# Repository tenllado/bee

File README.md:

# BEE board

A simple Raspberry pi expansion board, designed with educational purposes to be
used to learn low level IO programming or used it for simple driver development.
It adds to the raspberry Pi the following circuits:

- A 10 bits ADC with 8 channels (MCP3008), that can be connected to the SPI
  gpios using 5 jumpers, it is connected to CE0.

- A 10 bit DAC (MCP4911), that can also be connected to the SPI gpios using the
  same 5 jumpers, and gets connected to CE1.

- 3 simple led circuits, and 3 switch circuits that can be connected to any gpio
  pin with some cables.

- A piezo-electric buzzer that can be connected with jumpers to the pwm pins of
  the raspberry pi.

- A shifter register connected to 7 Segment display (with dot point).

- A UART connector for the FTDI-232-R cables to connect one of the UART devices
  of the Raspberry pi to a PC.

- A standard 20 pin JTAG connector for baremetal programming and in-circuit
  debug using OpenOCD.

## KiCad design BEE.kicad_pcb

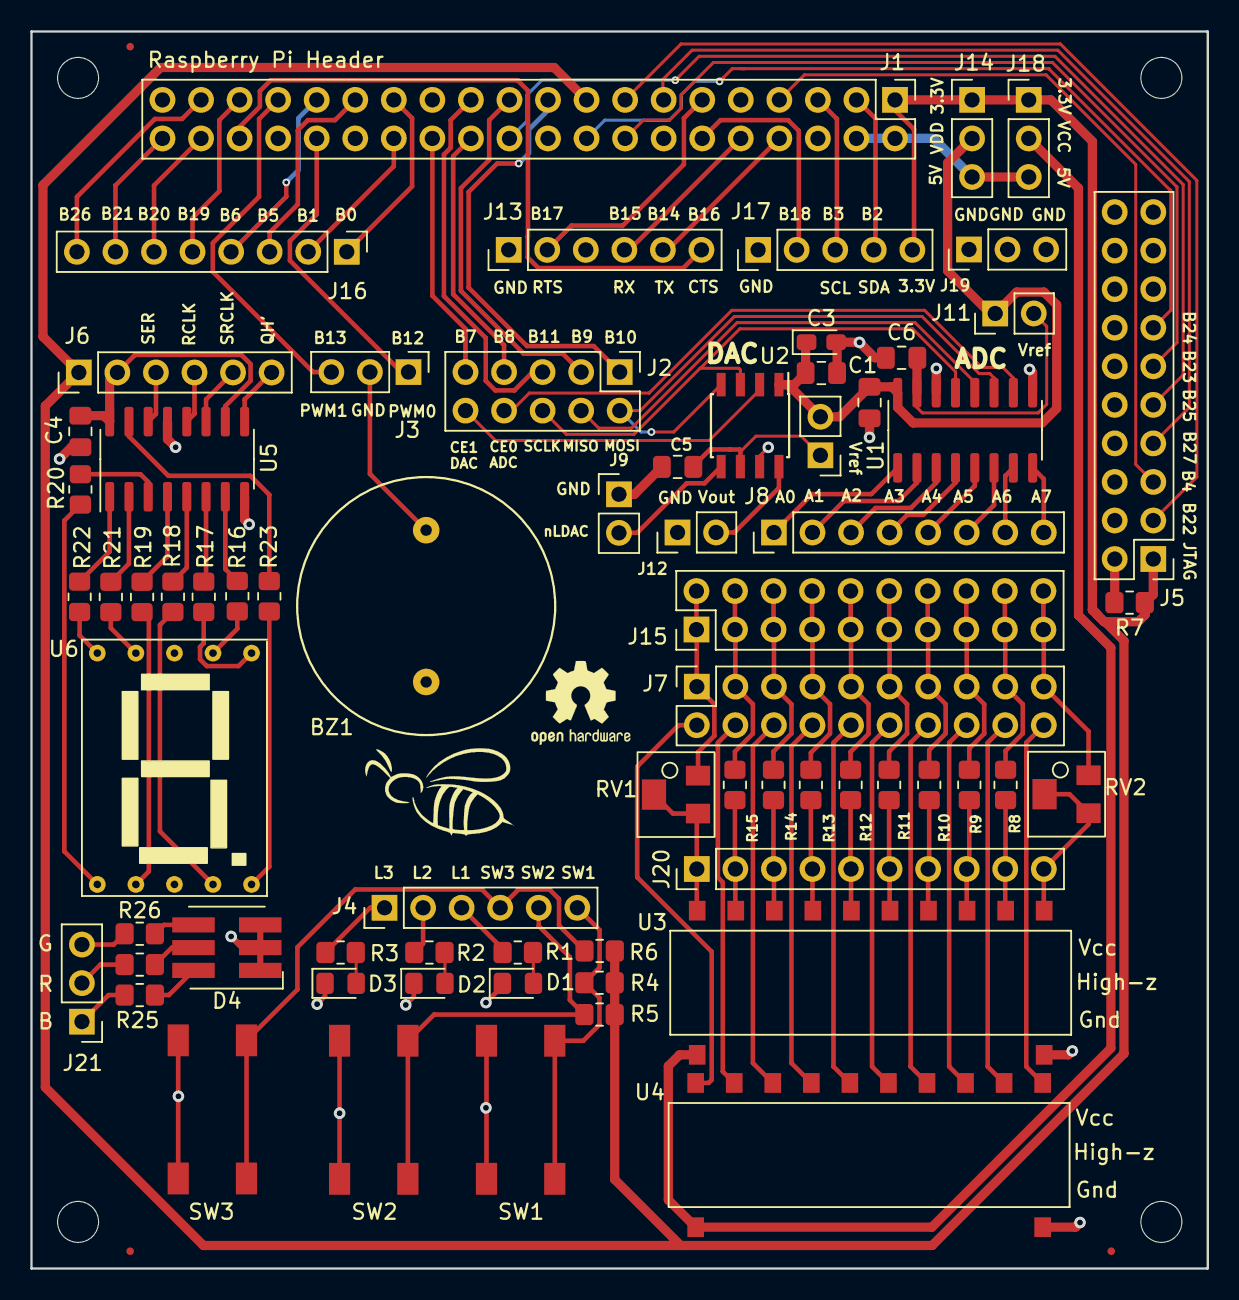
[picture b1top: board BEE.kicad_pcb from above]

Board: 2 copper layers, 77.5 x 81.5 mm, 79 parts (1 on the bottom side), 118 nets.

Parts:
BZ1: /re; Buzzer
C1, C6: 1uF; C_0805_2012Metric_Pad1.18x1.45mm_HandSolder
C2, C4, C5: 0.1uF; C_0805_2012Metric_Pad1.18x1.45mm_HandSolder
C3: 10uF; CP_EIA-2012-15_AVX-P_Pad1.30x1.05mm_HandSolder
D1, D2, D3: LED; LED_0805_2012Metric_Pad1.15x1.40mm_HandSolder
D4: LED_RGB; LED_RGB_5050-6
FID1, FID2, FID3: Fiducial; Fiducial_0.5mm_Dia_1mm_Outer
H1, H2, H3, H4: MountingHole; MountingHole_2.7mm_M2.5
J1: RPI1_header; PinHeader_2x20_P2.54mm_Vertical
J2: Conn_02x05_Odd_Even; PinHeader_2x05_P2.54mm_Vertical
J3, J14, J18, J19, J21: Conn_01x03; PinHeader_1x03_P2.54mm_Vertical
J4, J6, J13: Conn_01x06; PinHeader_1x06_P2.54mm_Vertical
J5, J15: Conn_02x10_Odd_Even; PinHeader_2x10_P2.54mm_Vertical
J7: Conn_02x10_Odd_Even; PinSocket_2x10_P2.54mm_Vertical
J8, J16: Conn_01x08; PinHeader_1x08_P2.54mm_Vertical
J9, J10, J11, J12: Conn_01x02; PinHeader_1x02_P2.54mm_Vertical
J17: Conn_01x05; PinHeader_1x05_P2.54mm_Vertical
J20: Conn_01x10; PinHeader_1x10_P2.54mm_Vertical
LOGO1: Logo_Open_Hardware_Small; OSHW-Logo2_7.3x6mm_SilkScreen
LOGO2: Logo_Open_Hardware_Small; bee_logo2
LOGO3: Logo_Open_Hardware_Small; UCMLogo_169_169
R1, R2, R3, R8, R9, R16, R17, R18, R19, R20, R21, R22, R23: 220; R_0805_2012Metric_Pad1.20x1.40mm_HandSolder
R4, R5, R6, R10, R11: 10k; R_0805_2012Metric_Pad1.20x1.40mm_HandSolder
R7: 0; R_0805_2012Metric_Pad1.20x1.40mm_HandSolder
R12, R13: 15k; R_0805_2012Metric_Pad1.20x1.40mm_HandSolder
R14, R15: 47k; R_0805_2012Metric_Pad1.20x1.40mm_HandSolder
R24: 280; R_0805_2012Metric_Pad1.20x1.40mm_HandSolder
R25, R26: 100; R_0805_2012Metric_Pad1.20x1.40mm_HandSolder
RV1, RV2: 100k; POT_PVG5A
SW1, SW2, SW3: SW_Push; PushButton
U1: MCP3008; SOIC-16_3.9x9.9mm_P1.27mm
U2: MCP4911; SOIC-8_3.9x4.9mm_P1.27mm
U3, U4: Dip_10xsp3t; dip_10xsp3t
U5: 74AHC595; SOIC-16_3.9x9.9mm_P1.27mm
U6: Display_7Segments; 7segments

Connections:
+3V3: J1.1 (+3.3V), J1.17 (+3.3V), J5.1, J6.1, J14.1, J17.5, J18.1, R4.1, R5.1, R6.1, R7.1
+5V: J1.2 (+5V), J1.4 (+5V), J14.3, J18.3
/BCM0: J1.27 (BCM0), J16.1
/BCM1: J1.28 (BCM1), J16.2
/BCM2_SDA: J1.3 (BCM2_SDA), J17.4
/BCM3_SCL: J1.5 (BCM3_SCL), J17.3
/BCM4_TDI: J1.7 (BCM4_TDI), J5.5
/BCM5: J1.29 (BCM5), J16.3
/BCM6: J1.31 (BCM6), J16.4
/BCM7_CE1: J1.26 (BCM7_CE1), J2.9
/BCM8_CE0: J1.24 (BCM8_CE0), J2.7
/BCM9_MISO: J1.21 (BCM9_MISO), J2.3
/BCM10_MOSI: J1.19 (BCM10_MOSI), J2.1
/BCM11_SCLK: J1.23 (BCM11_SCLK), J2.5
/BCM12_PWM0: J1.32 (BCM12), J3.1
/BCM13_PWM1: J1.33 (BCM13), J3.3
/BCM14_TX: J1.8 (BCM14_TX), J13.5
/BCM15_RX: J1.10 (BCM15_RX), J13.4
/BCM16_CTS: J1.36 (BCM16), J13.6
/BCM17_RTS: J1.11 (BCM17), J13.2
/BCM18: J1.12 (BCM18_PWM), J17.2
/BCM19: J1.35 (BCM19), J16.5
/BCM20: J1.38 (BCM20), J16.6
/BCM21: J1.40 (BCM21), J16.7
/BCM22_TRST: J1.15 (BCM22_TRST), J5.3
/BCM23_RTCK: J1.16 (BCM23), J5.11
/BCM24_TDO: J1.18 (BCM24_TDO), J5.13
/BCM25_TCK: J1.22 (BCM25_TCK), J5.9
/BCM26: J1.37 (BCM26), J16.8
/BCM27_TMS: J1.13 (BCM27_TMS), J5.7
/CE_ADC: J2.8, U1.10 (~CS/SHDN)
/CE_DAC: J2.10, U2.2 (~CS)
/L1: J4.3, R1.1
/L2: J4.2, R2.1
/L3: J4.1, R3.1
/MISO: J2.4, U1.12 (Dout)
/MOSI: J2.2, U1.11 (Din), U2.4 (SDI)
/QH': J6.6, U5.9 (QH')
/RCLK: J6.4, U5.12 (RCLK)
/SCLK: J2.6, U1.13 (CLK), U2.3 (SCK)
/SER: J6.3, U5.14 (SER)
/SRCLK: J6.5, U5.11 (SRCLK)
/SW1: J4.6, R4.2, SW1.1
/SW2: J4.5, R5.2, SW2.1
/SW3: J4.4, R6.2, SW3.1
GND: BZ1.2 (+), C1.2, C2.2, C3.2, C4.2, C5.1, C6.1, D1.1 (K), D2.1 (K), D3.1 (K), D4.1 (RK), D4.3 (GK), D4.5 (BK), J1.6 (Gnd), J1.9 (Gnd), J1.14 (Gnd), J1.20 (Gnd), J1.25 (Gnd), J1.30 (Gnd), J1.34 (Gnd), J1.39 (Gnd), J5.4, J5.6, J5.8, J5.10, J5.12, J5.14, J5.16, J5.18, J5.20, J9.1, J12.1, J13.1, J17.1, J19.1, J19.2, J19.3, SW1.2, SW2.2, SW3.2, U1.9 (DGND), U1.14 (AGND), U2.7 (Vss), U3.11 (-), U4.11 (-), U5.8 (GND), U5.13 (~OE), U6.3 (CA), U6.8 (CA)
unnamed: BZ1.1 (-), J3.2
unnamed: C5.2, J10.1, U2.6 (Vref)
unnamed: C6.2, J11.2, U1.15 (Vref)
unnamed: D1.2 (A), R1.2
unnamed: D2.2 (A), R2.2
unnamed: D3.2 (A), R3.2
unnamed: D4.2 (RA), R25.2
unnamed: D4.4 (GA), R24.2
unnamed: D4.6 (BA), R26.2
unnamed: J5.2, R7.2
unnamed: J7.2, U4.1
unnamed: J7.4, U4.2
unnamed: J7.6, U4.3
unnamed: J7.8, U4.4
unnamed: J7.10, U4.5
unnamed: J7.12, U4.6
unnamed: J7.14, U4.7
unnamed: J7.16, U4.8
unnamed: J7.18, U4.9
unnamed: J7.20, U4.10
unnamed: J8.1, U1.1 (CH0)
unnamed: J8.2, U1.2 (CH1)
unnamed: J8.3, U1.3 (CH2)
unnamed: J8.4, U1.4 (CH3)
unnamed: J8.5, U1.5 (CH4)
unnamed: J8.6, U1.6 (CH5)
unnamed: J8.7, U1.7 (CH6)
unnamed: J8.8, U1.8 (CH7)
unnamed: J9.2, U2.5 (~LDAC)
unnamed: J12.2, U2.8 (Vout)
unnamed: J7.1, J15.1, J15.2, RV1.3
unnamed: J7.3, J15.3, J15.4, R15.2
unnamed: J7.5, J15.5, J15.6, R14.2
unnamed: J7.7, J15.7, J15.8, R13.2
unnamed: J7.9, J15.9, J15.10, R12.1
unnamed: J7.11, J15.11, J15.12, R11.2
unnamed: J7.13, J15.13, J15.14, R10.1
unnamed: J7.15, J15.15, J15.16, R9.1
unnamed: J7.17, J15.17, J15.18, R8.1
unnamed: J7.19, J15.19, J15.20, RV2.3
unnamed: J20.1, RV1.1, RV1.2, U3.1
unnamed: J20.2, R15.1, U3.2
unnamed: J20.3, R14.1, U3.3
unnamed: J20.4, R13.1, U3.4
unnamed: J20.5, R12.2, U3.5
unnamed: J20.6, R11.1, U3.6
unnamed: J20.7, R10.2, U3.7
unnamed: J20.8, R9.2, U3.8
unnamed: J20.9, R8.2, U3.9
unnamed: J20.10, RV2.1, RV2.2, U3.10
unnamed: J21.1, R25.1
unnamed: J21.2, R24.1
unnamed: J21.3, R26.1
unnamed: R16.1, U6.7 (A)
unnamed: R16.2, U5.7 (QH)
unnamed: R17.1, U6.6 (B)
unnamed: R17.2, U5.6 (QG)
unnamed: R18.1, U6.4 (C)
unnamed: R18.2, U5.5 (QF)
unnamed: R19.1, U6.2 (D)
unnamed: R19.2, U5.4 (QE)
unnamed: R20.1, U6.1 (E)
unnamed: R20.2, U5.3 (QD)
unnamed: R21.1, U6.9 (F)
unnamed: R21.2, U5.2 (QC)
unnamed: R22.1, U6.10 (G)
unnamed: R22.2, U5.1 (QB)
unnamed: R23.1, U6.5 (DP)
unnamed: R23.2, U5.15 (QA)
VCC: J18.2, U3.12 (+), U4.12 (+)
VD: C4.1, J6.2, U5.10 (~SRCLR), U5.16 (VCC)
VDD: C1.1, C2.1, C3.1, J10.2, J11.1, J14.2, U1.16 (Vdd), U2.1 (Vdd)

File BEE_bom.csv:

Reference, Quantity, Value, Footprint, Datasheet, Distributor, Distributor PN, Distributor link, Manufacturer, Manufacturer PN
BZ1 ,1,"/re","BEElib:Buzzer","https://www.mouser.es/datasheet/2/400/iezoelectronic_buzzer_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","Mouser","810-PS1720P02","https://www.mouser.es/ProductDetail/TDK/PS1720P02?qs=%2Fha2p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","TDK","PS1720P02"
C1 ,1,"1uF","Capacitor_SMD:C_0805_2012Metric_Pad1.15x1.40mm_HandSolder","https://www.mouser.es/datasheet/2/212/KEM_C1002_X7R_SMD-1102033.pdf","Mouser"," 80-C0805C105K4R","https://www.mouser.es/ProductDetail/KEMET/C0805C105K4RACTU?q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","KEMET","C0805C105K4RACTU"
C2 ,1,"0.1uF","Capacitor_SMD:C_0805_2012Metric_Pad1.15x1.40mm_HandSolder","https://www.mouser.es/datasheet/2/212/KEM_C1002_X7R_SMD-1102033.pdf","Mouser","80-C0805C104K3R","https://www.mouser.es/ProductDetail/KEMET/C0805C104K3RACTU?q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","KEMET","C0805C104K3RACTU"
C3 ,1,"10uF","Capacitor_SMD:C_0805_2012Metric_Pad1.15x1.40mm_HandSolder","https://www.mouser.es/datasheet/2/40/TAJ_LOW_PROFILE-932651.pdf","Mouser"," 581-TAJP106K006RNJ ","https://www.mouser.es/ProductDetail/AVX/TAJP106K006RNJ?qs=q%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","AVX","TAJP106K006RNJ "
D1 D2 D3 ,3,"LED","LED_SMD:LED_0805_2012Metric_Pad1.15x1.40mm_HandSolder","https://www.mouser.es/datasheet/2/445/150080RS75000-368622.pdf","Mouser"," 710-150080RS75000 ","https://www.mouser.es/ProductDetail/Wurth-Elektronik/150080R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","Wurth Elektronik","150080RS75000"
FID1 FID2 FID3 ,3,"Fiducial","Fiducial:Fiducial_0.5mm_Dia_1mm_Outer",""
H1 H2 H3 H4 ,4,"MountingHole","MountingHole:MountingHole_2.7mm_M2.5","~"
J1 ,1,"RPI1_header","Connector_PinHeader_2.54mm:PinHeader_2x20_P2.54mm_Vertical","https://www.mouser.es/datasheet/2/418/NG_CD_146254_J2-1238606.pdf","Mouser","571-7-146254-0","https://www.mouser.es/ProductDetail/TE-Connectivity-AMP/7-14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","TE Connectivity / AMP","7-146254-0"
J16 ,1,"Conn_01x08","Connector_PinHeader_2.54mm:PinHeader_1x08_P2.54mm_Vertical","https://www.mouser.es/datasheet/2/18/68000-1266375.pdf","Mouser","649-68000-408HLF","https://www.mouser.es/ProductDetail/Amphenol-FCI/68000-408HL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","Amphenol FCI ","68000-408HLF"
J14 J17 J18 ,3,"Conn_01x03","Connector_PinHeader_2.54mm:PinHeader_1x03_P2.54mm_Vertical","https://www.mouser.es/datasheet/2/18/68000-1266375.pdf","Mouser","649-68001-403HLF","https://www.mouser.es/ProductDetail/Amphenol-FCI/68001-403HL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","Amphenol FCI","68001-403HLF"
J2 ,1,"Conn_02x05_Odd_Even","Connector_PinHeader_2.54mm:PinHeader_2x05_P2.54mm_Vertical","https://www.mouser.es/datasheet/2/18/67996-1142923.pdf","Mouser","649-67997-210HLF ","https://www.mouser.es/ProductDetail/Amphenol-FCI/67997-210HL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","Amphenol FCI","67997-210HLF "
J3 ,1,"Conn_02x03_Odd_Even","Connector_PinHeader_2.54mm:PinHeader_2x03_P2.54mm_Vertical","https://www.mouser.es/datasheet/2/276/0879140804_PCB_HEADERS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","Mouser","538-87914-0616 ","https://www.mouser.es/ProductDetail/Molex/87914-0616?qs=sGAE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","Molex","87914-0616"
J13 J4 ,2,"Conn_01x06","Connector_PinHeader_2.54mm:PinHeader_1x06_P2.54mm_Vertical","https://www.mouser.es/datasheet/2/276/0022284060_PCB_HEADERS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","Mouser"," 538-22-28-4060 ","https://www.mouser.es/ProductDetail/Molex/22-28-4060?qs=sGAE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","Molex","22-28-4060"
J5 ,1,"Conn_02x10_Odd_Even","Connector_PinHeader_2.54mm:PinHeader_2x10_P2.54mm_Vertical","https://www.mouser.es/datasheet/2/18/77313-1266357.pdf","Mouser","649-77313-418-20LF ","https://www.mouser.es/ProductDetail/Amphenol-FCI/77313-418-2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","Amphenol FCI ","77313-418-20LF"
J7 ,1,"Conn_02x08_Odd_Even","Connector_PinSocket_2.54mm:PinSocket_2x08_P2.54mm_Vertical","https://www.mouser.es/datasheet/2/276/0901512116_PCB_RECEPTA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","Mouser"," 538-90151-2116 ","https://www.mouser.es/ProductDetail/Molex/90151-2116?qs=sGAE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","Molex","90151-2116 "
J8 ,1,"Conn_02x08_Top_Bottom","Connector_PinHeader_2.54mm:PinHeader_2x08_P2.54mm_Vertical","https://www.amphenol-icc.com/media/wysiwyg/files/documentati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","Mouser"," 649-67996-416HLF ","https://www.mouser.es/ProductDetail/Amphenol-FCI/67996-416HL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","Amphenol FCI","67996-416HLF"
J10 J11 J12 J9 ,4,"Conn_01x02","Connector_PinHeader_2.54mm:PinHeader_1x02_P2.54mm_Vertical","https://www.mouser.es/datasheet/2/18/68000-1266375.pdf","Mouser","649-68001-402HLF","https://www.mouser.es/ProductDetail/Amphenol-FCI/68001-402HL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","Amphenol FCI","68001-402HLF"
LOGO1 ,1,"Logo_Open_Hardware_Small","Symbol:OSHW-Logo2_7.3x6mm_SilkScreen","~"
LOGO2 ,1,"Logo_Open_Hardware_Small","BEElib:bee_logo2","~"
LOGO3 ,1,"Logo_Open_Hardware_Small","BEElib:UCMLogo_169_169","~"
R10 R14 ,2,"15k","Resistor_SMD:R_0805_2012Metric_Pad1.15x1.40mm_HandSolder","https://www.mouser.es/datasheet/2/427/crcwce3-1223726.pdf","Mouser","71-CRCW080515K0FKEAC","https://www.mouser.es/ProductDetail/Vishay-Dale/CRCW080515K0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","Vishay / Dale","CRCW080515K0FKEAC"
R11 R15 ,2,"47k","Resistor_SMD:R_0805_2012Metric_Pad1.15x1.40mm_HandSolder","https://www.mouser.es/datasheet/2/427/crcwce3-1223726.pdf","Mouser","71-CRCW080547K0FKEAC","https://www.mouser.es/ProductDetail/Vishay-Dale/CRCW080547K0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","Vishay / Dale","CRCW080547K0FKEAC"
R1 R12 R2 R3 R8 ,5,"220","Resistor_SMD:R_0805_2012Metric_Pad1.15x1.40mm_HandSolder","https://www.mouser.es/datasheet/2/427/crcwce3-1223726.pdf","Mouser"," 71-CRCW0805220RFKEAC ","https://www.mouser.es/ProductDetail/Vishay-Dale/CRCW0805220R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","Vishay / Dale ","CRCW0805220RFKEAC "
R13 R4 R5 R6 R9 ,5,"10k","Resistor_SMD:R_0805_2012Metric_Pad1.15x1.40mm_HandSolder","https://www.mouser.es/datasheet/2/427/crcwce3-1223726.pdf","Mouser","71-CRCW080510K0FKEAC","https://www.mouser.es/ProductDetail/Vishay-Dale/CRCW080510K0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","Vishay / Dale ","CRCW080510K0FKEAC"
R7 ,1,"0","Resistor_SMD:R_0805_2012Metric_Pad1.15x1.40mm_HandSolder","https://www.mouser.es/datasheet/2/447/PYu-AC_51_RoHS_L_7-171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","Mouser"," 603-AC0805FR-070RL","https://www.mouser.es/ProductDetail/Yageo/AC0805FR-070RL?qs=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","Yageo","AC0805FR-070RL"
SW1 SW2 SW3 ,3,"SW_Push","BEElib:Push Button","https://www.mouser.es/datasheet/2/140/P090002-267756.pdf","Mouser","612-LL3301NF065QG ","https://www.mouser.es/ProductDetail/E-Switch/LL3301NF065QG?q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","E-Switch","LL3301NF065QG "
U1 ,1,"MCP3008","Package_SO:SOIC-16_3.9x9.9mm_P1.27mm","http://ww1.microchip.com/downloads/en/DeviceDoc/21295d.pdf","Mouser","579-MCP3008T-I/SL ","https://www.mouser.es/ProductDetail/Microchip-Technology/MCP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","Microchip Technologies","MCP3008T-I/S"
U2 ,1,"MCP4911","Package_SO:SOIC-8_3.9x4.9mm_P1.27mm","http://ww1.microchip.com/downloads/en/DeviceDoc/22248a.pdf","Mouser","579-MCP4911-E/SN","https://www.mouser.es/ProductDetail/Microchip-Technology/MCP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","Microchip Technologies","MCP4911-E/SN "

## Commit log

2019-10-04 no signal reorder
2019-10-04 small change
2019-10-05 wip: some traces added
2019-10-06 wip:pcb routed, raspi header can be moved right
2019-10-06 wip: routed, raspi header can be moved right
2019-10-07 wip some traces re-routed
2019-10-07 wip: with mounting holes, board a little bit bigger
2019-10-08 uart connector with jumpers to select crossed or direct connection. rerouted and labeled
2019-10-08 additional via for led circuits
2019-10-09 reposition, reroute, removed cross connector for UART. Labeled
2019-10-09 Fiducials and Logos
2019-10-09 Added description to README
2019-10-09 UCM logo and github repo url
2019-10-10 some traces redone for better return path on ground plane. Reposition of fiducials.
2019-10-11 return current loops reduced
2019-10-13 self made logo
2019-10-13 inskscape source for the logo
2019-10-13 removed old logo
2019-10-13 github url of the project in the schematic
2019-10-15 revision of fab layer. Ref designator in fab layer. bom
2019-10-16 mounting holes 2.7mm
2019-10-16 gerbers and fill zones update
2019-10-18 Gerbers update
2019-11-13 changing some minor things after first prototype test
2020-01-17 wip Resistors and new pin connectors
2020-01-18 separate vcc connector moved down
2020-01-19 vcc down with double socket for external sensors
2020-01-19 new position and routes for resistors for sensors
2020-01-19 replace and reroute: jtag signals on the sides
2020-01-19 Remove connector with gnd, +3.3v and +5V, and reroute
2020-01-19 some extra labels in silk screen
2020-01-19 small obsesive changes
2020-01-20 minor mod, track simplified
2020-01-20 jtag connector rotated, jtag signals on the right
2020-01-20 some tracks redone, not sure if it is any better
2020-01-20 minor placement and labeling modifications
2020-03-15 Gerbers for new revision
2020-10-19 component changes
2020-10-19 BOM files
2022-03-08 last changes
2022-03-09 first version with display and dip switches
2022-03-09 test of alternative layout
2022-03-10 vertical block for display driver
2022-03-10 Bypass cap for Shifter, DAC cap symbol fix, DAC out pin headers reorganization, labels and fab layer cleanup.
2022-03-10 Changelog added and README update for version 2
2022-03-11 independent polarization network
2022-03-11 3D models for dip switches
2022-03-11 Extra pin headers in polarization network and 3d models
2022-03-11 Bit endianness change in display shifter, and some other minor changes to that driver
2022-03-11 Changelog update for 2.0 release
2022-03-11 fab layer cleanup
2022-03-11 ucm logo and project moved
2022-03-13 RGB Led and J17 adaptation to pimoroni breakouts
2022-03-14 small rerouting of rgb led module
2022-03-15 Migration to kicad 6.0
2022-03-23 changed RGB led by a bigger 5050 one
2022-03-23 D4 pin numbering adjusted on schematic and footprint, according to datasheet
2022-03-24 labels for RGB led
2022-04-21 BEE 2.0 final touches
2022-04-21 BEE.xml
2022-04-21 remove Gerbers files from repo
2022-04-25 renombrado de Manufacturer PN a MPN. borrado ficheros versión anterior
2022-04-25 update to version 6
2022-04-25 update to kicad 6
2022-05-04 changes for fabrication
